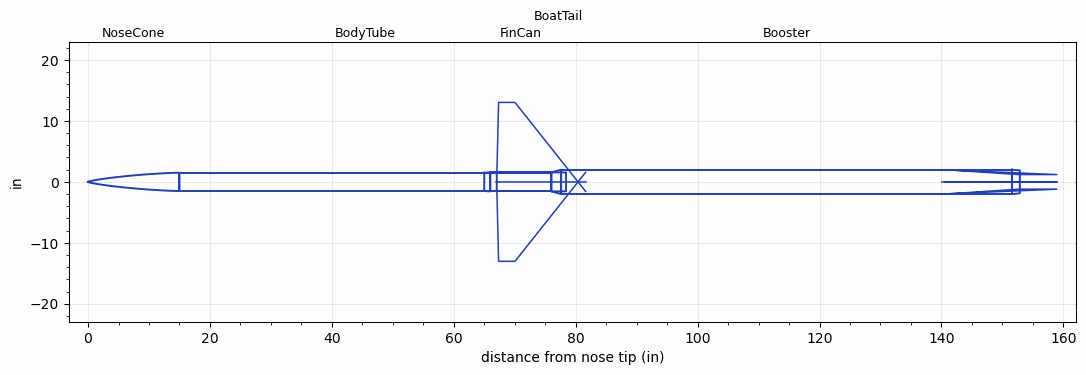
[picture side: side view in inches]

<RASAeroDocument>
 <FileVersion>2</FileVersion>
 <RocketDesign>
  <NoseCone>
   <Length>15</Length>
   <Diameter>3</Diameter>
   <Shape>Von Karman Ogive</Shape>
   <Location>0</Location>
  </NoseCone>
  <BodyTube>
   <Length>61</Length>
   <Diameter>3</Diameter>
   <Location>15</Location>
  </BodyTube>
  <FinCan>
   <Length>10</Length>
   <Diameter>3.12</Diameter>
   <InsideDiameter>3</InsideDiameter>
   <Location>76</Location>
   <ShoulderLength>1</ShoulderLength>
   <Offset>-10</Offset>
   <Fin>
    <Count>4</Count>
    <Chord>14.625797</Chord>
    <Span>-14.593677</Span>
    <SweepDistance>0.35238178</SweepDistance>
    <TipChord>2.6858533</TipChord>
    <Thickness>0.2483</Thickness>
    <LERadius>0.05</LERadius>
    <Location>9</Location>
    <AirfoilSection>Hexagonal Blunt Base</AirfoilSection>
    <FX1>0.69</FX1>
    <FX3>0.81</FX3>
   </Fin>
  </FinCan>
  <BoatTail>
   <Length>2.42</Length>
   <Diameter>3.12</Diameter>
   <RearDiameter>3.1</RearDiameter>
   <Location>76</Location>
  </BoatTail>
  <Booster>
   <Length>73.96</Length>
   <Diameter>4</Diameter>
   <InsideDiameter>3.12</InsideDiameter>
   <Location>76</Location>
   <ShoulderLength>1.6122</ShoulderLength>
   <BoattailLength>1.2842</BoattailLength>
   <BoattailRearDiameter>3.75</BoattailRearDiameter>
   <Fin>
    <Count>4</Count>
    <Chord>-0.48662464</Chord>
    <Span>-0.80158464</Span>
    <SweepDistance>12.148756</SweepDistance>
    <TipChord>6.1978226</TipChord>
    <Thickness>0.2483</Thickness>
    <LERadius>0.05</LERadius>
    <Location>11</Location>
    <AirfoilSection>Hexagonal Blunt Base</AirfoilSection>
    <FX1>0.69</FX1>
    <FX3>0.81</FX3>
   </Fin>
  </Booster>
  <Surface>Rough Camouflage Paint</Surface>
  <ModifiedBarrowman>True</ModifiedBarrowman>
  <Turbulence>False</Turbulence>
  <UseBooster1>False</UseBooster1>
  <UseBooster2>False</UseBooster2>
 </RocketDesign>
 <LaunchSite>
  <Altitude>2500</Altitude>
  <Pressure>0</Pressure>
  <RodAngle>3</RodAngle>
  <RodLength>20</RodLength>
  <Temperature>95</Temperature>
  <WindSpeed>5</WindSpeed>
 </LaunchSite>
 <Recovery>
  <Altitude1>1000</Altitude1>
  <Altitude2>1000</Altitude2>
  <DeviceType1>None</DeviceType1>
  <DeviceType2>None</DeviceType2>
  <Event1>False</Event1>
  <Event2>False</Event2>
  <Size1>1</Size1>
  <Size2>1</Size2>
  <EventType1>None</EventType1>
  <EventType2>None</EventType2>
  <CD1>1.33</CD1>
  <CD2>1.33</CD2>
 </Recovery>
 <SimulationList>
  <Simulation>
   <SustainerEngine>M1260  (MIT)</SustainerEngine>
   <SustainerLaunchWt>12.003898</SustainerLaunchWt>
   <SustainerNozzleDiameter>2.95</SustainerNozzleDiameter>
   <SustainerCG>53.15</SustainerCG>
   <SustainerIgnitionDelay>6</SustainerIgnitionDelay>
   <Booster1Engine>N2827  (MIT-Propteam)</Booster1Engine>
   <Booster1LaunchWt>62.294276</Booster1LaunchWt>
   <Booster1SeparationDelay>0</Booster1SeparationDelay>
   <Booster1IgnitionDelay>0</Booster1IgnitionDelay>
   <Booster1CG>102.58</Booster1CG>
   <Booster1NozzleDiameter>2.5</Booster1NozzleDiameter>
   <IncludeBooster1>True</IncludeBooster1>
   <Booster2Delay>0</Booster2Delay>
   <IncludeBooster2>False</IncludeBooster2>
   <TimetoApogee>64.78609</TimetoApogee>
   <MaxAltitude>67796.01</MaxAltitude>
   <MaxVelocity>2853.142</MaxVelocity>
  </Simulation>
 </SimulationList>
</RASAeroDocument>
